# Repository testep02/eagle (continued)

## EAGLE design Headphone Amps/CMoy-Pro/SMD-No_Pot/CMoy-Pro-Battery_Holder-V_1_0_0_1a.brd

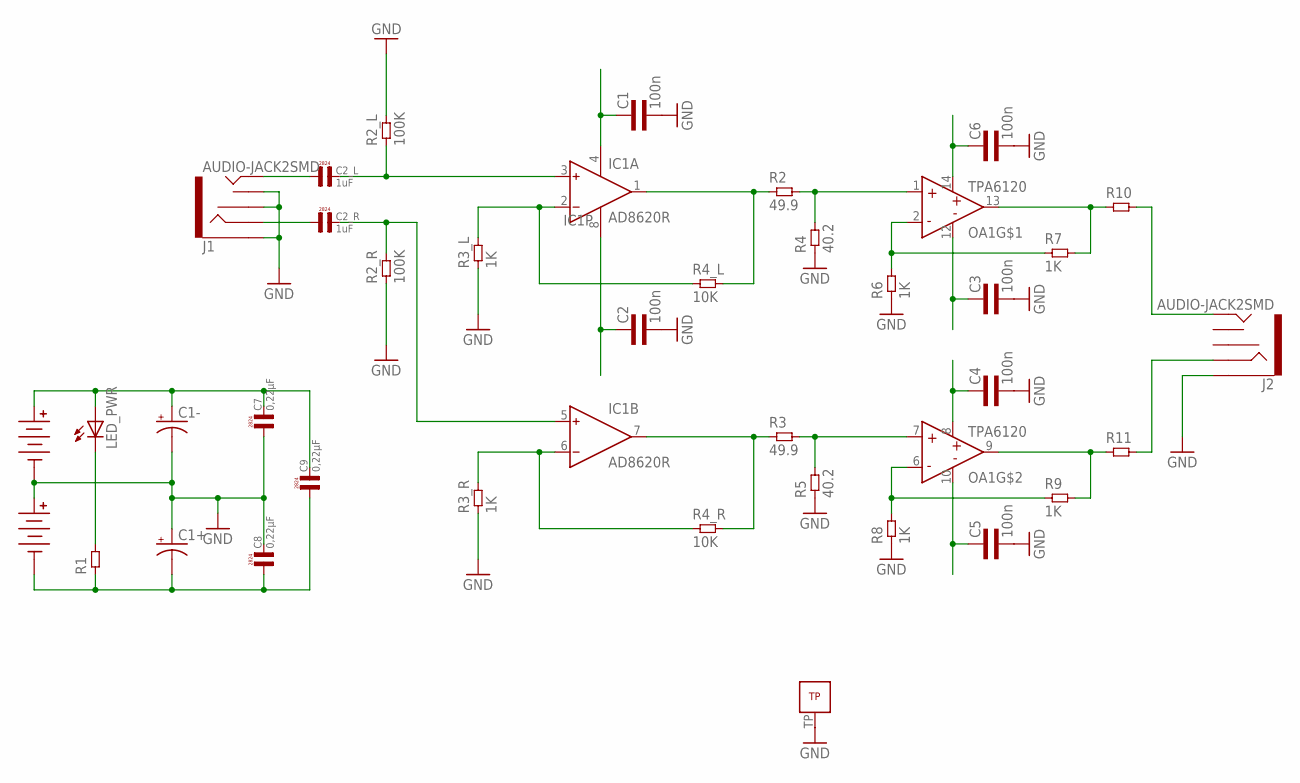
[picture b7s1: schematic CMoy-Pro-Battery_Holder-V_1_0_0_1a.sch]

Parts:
BATT1, BATT2: BATT_9V; 9V_FEMALE
C1, C2, C3, C4, C5, C6: 100n; 0603L3
C1+, C1-: CPOL-US140CLH-1010; 140CLH-1010
C2_L, C2_R: 1uF; L7,2
C7, C8, C9: 0,22µF; L7,2
IC1: AD8620R; SO8
J1, J2: AUDIO-JACK2SMD; AUDIO-JACK-3.5MM-SMD
LED_PWR: LEDCHIP-LED0603; CHIP-LED0603
OA1: TPA6120QFN; S-PVQFN-N14
R1: RES0603L3; 0603L3
R2, R3: 49.9; 0603L3
R2_L, R2_R: 100K; 0603L3
R3_L, R3_R, R6, R7, R8, R9: 1K; 0603L3
R4, R5: 40.2; 0603L3
R4_L, R4_R: 10K; 0603L3
R10, R11: RES1206L3; 1206L3

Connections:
GND: BATT1.N1 (NEG), BATT1.N2 (NEG), BATT1.N3 (NEG), BATT2.P1 (POS), BATT2.P2 (POS), BATT2.P3 (POS), C1.P$2 (2), C1+.+, C1-.-, C2.P$2 (2), C3.P$2 (2), C4.P$2 (2), C5.P$2 (2), C6.P$2 (2), C7.P$1 (1), C8.P$2 (2), J1.RSH, J1.SLEEVE, J1.TSH, J2.SLEEVE, OA1.TP, R2_L.P$2 (2), R2_R.P$1 (1), R3_L.P$1 (1), R3_R.P$1 (1), R4.P$1 (1), R5.P$1 (1), R6.P$1 (1), R8.P$1 (1)
HP_L: C2_R.P$1 (1), J1.RING
HP_R: C2_L.P$1 (1), J1.TIP
IN_L: C2_R.P$2 (2), IC1.5 (IN+), R2_R.P$2 (2)
IN_R: C2_L.P$2 (2), IC1.3 (IN+), R2_L.P$1 (1)
unnamed: LED_PWR.C, R1.P$2 (2)
unnamed: OA1.1 (IN+), R2.P$2 (2), R4.P$2 (2)
unnamed: OA1.7 (IN+), R3.P$2 (2), R5.P$2 (2)
unnamed: OA1.2 (IN-), R6.P$2 (2), R7.P$1 (1)
unnamed: IC1.2 (IN-), R3_L.P$2 (2), R4_L.P$1 (1)
unnamed: IC1.6 (IN-), R3_R.P$2 (2), R4_R.P$1 (1)
unnamed: OA1.13 (OUT), R7.P$2 (2), R10.1
unnamed: OA1.6 (IN-), R8.P$2 (2), R9.P$1 (1)
unnamed: OA1.9 (OUT), R9.P$2 (2), R11.1
unnamed: J2.TIP, R10.2
unnamed: J2.RING, R11.2
OUT_L: IC1.1 (OUT), R2.P$1 (1), R4_L.P$2 (2)
OUT_R: IC1.7 (OUT), R3.P$1 (1), R4_R.P$2 (2)
V+: BATT1.P1 (POS), BATT1.P2 (POS), BATT1.P3 (POS), C1-.+, C2.P$1 (1), C4.P$1 (1), C6.P$1 (1), C7.P$2 (2), C9.P$2 (2), IC1.8 (V+), LED_PWR.A, OA1.8 (V+), OA1.14 (V+)
V-: BATT2.N1 (NEG), BATT2.N2 (NEG), BATT2.N3 (NEG), C1.P$1 (1), C1+.-, C3.P$1 (1), C5.P$1 (1), C8.P$1 (1), C9.P$1 (1), IC1.4 (V-), OA1.10 (V-), OA1.12 (V-), R1.P$1 (1)

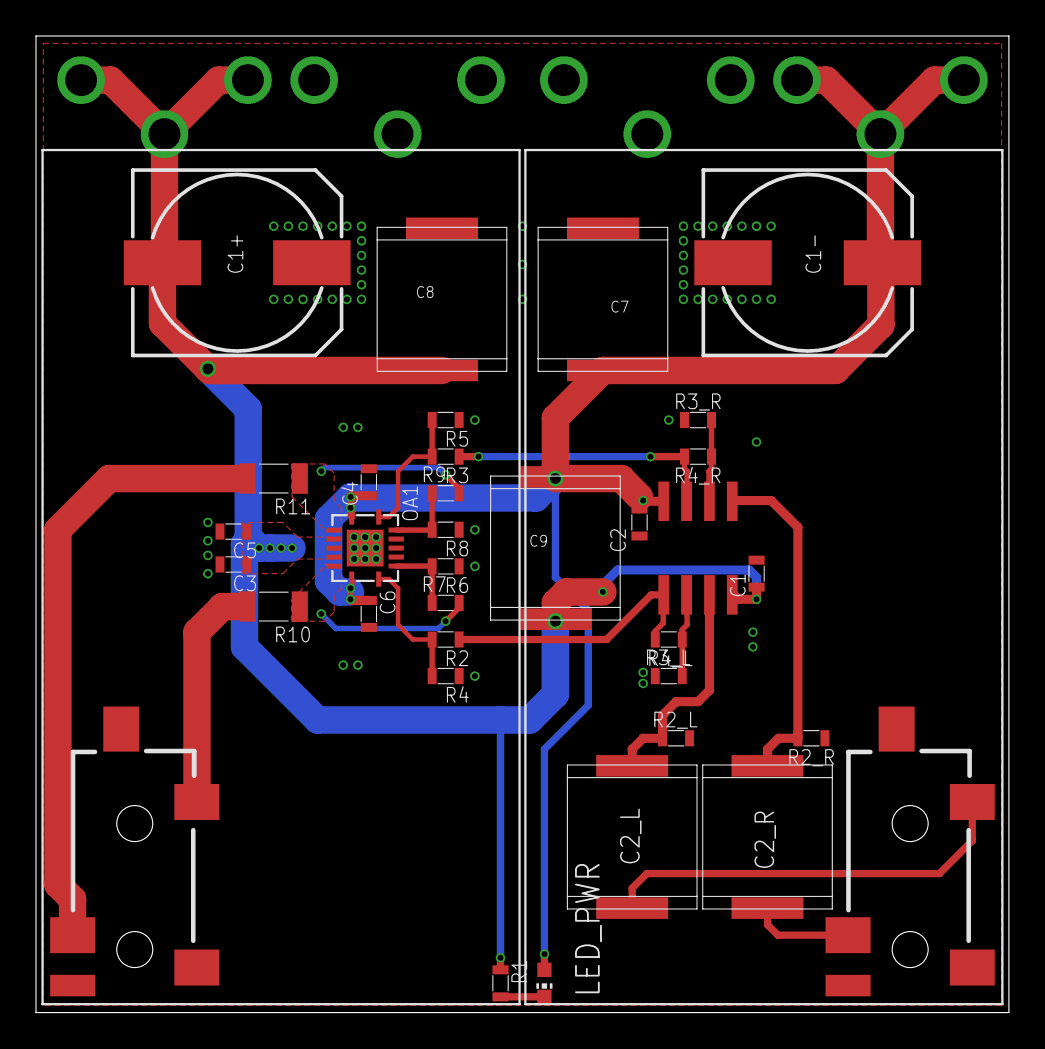
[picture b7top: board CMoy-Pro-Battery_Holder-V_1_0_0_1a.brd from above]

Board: 2 copper layers, 54.1 x 54.3 mm, 37 parts (0 on the bottom side), 20 nets.
